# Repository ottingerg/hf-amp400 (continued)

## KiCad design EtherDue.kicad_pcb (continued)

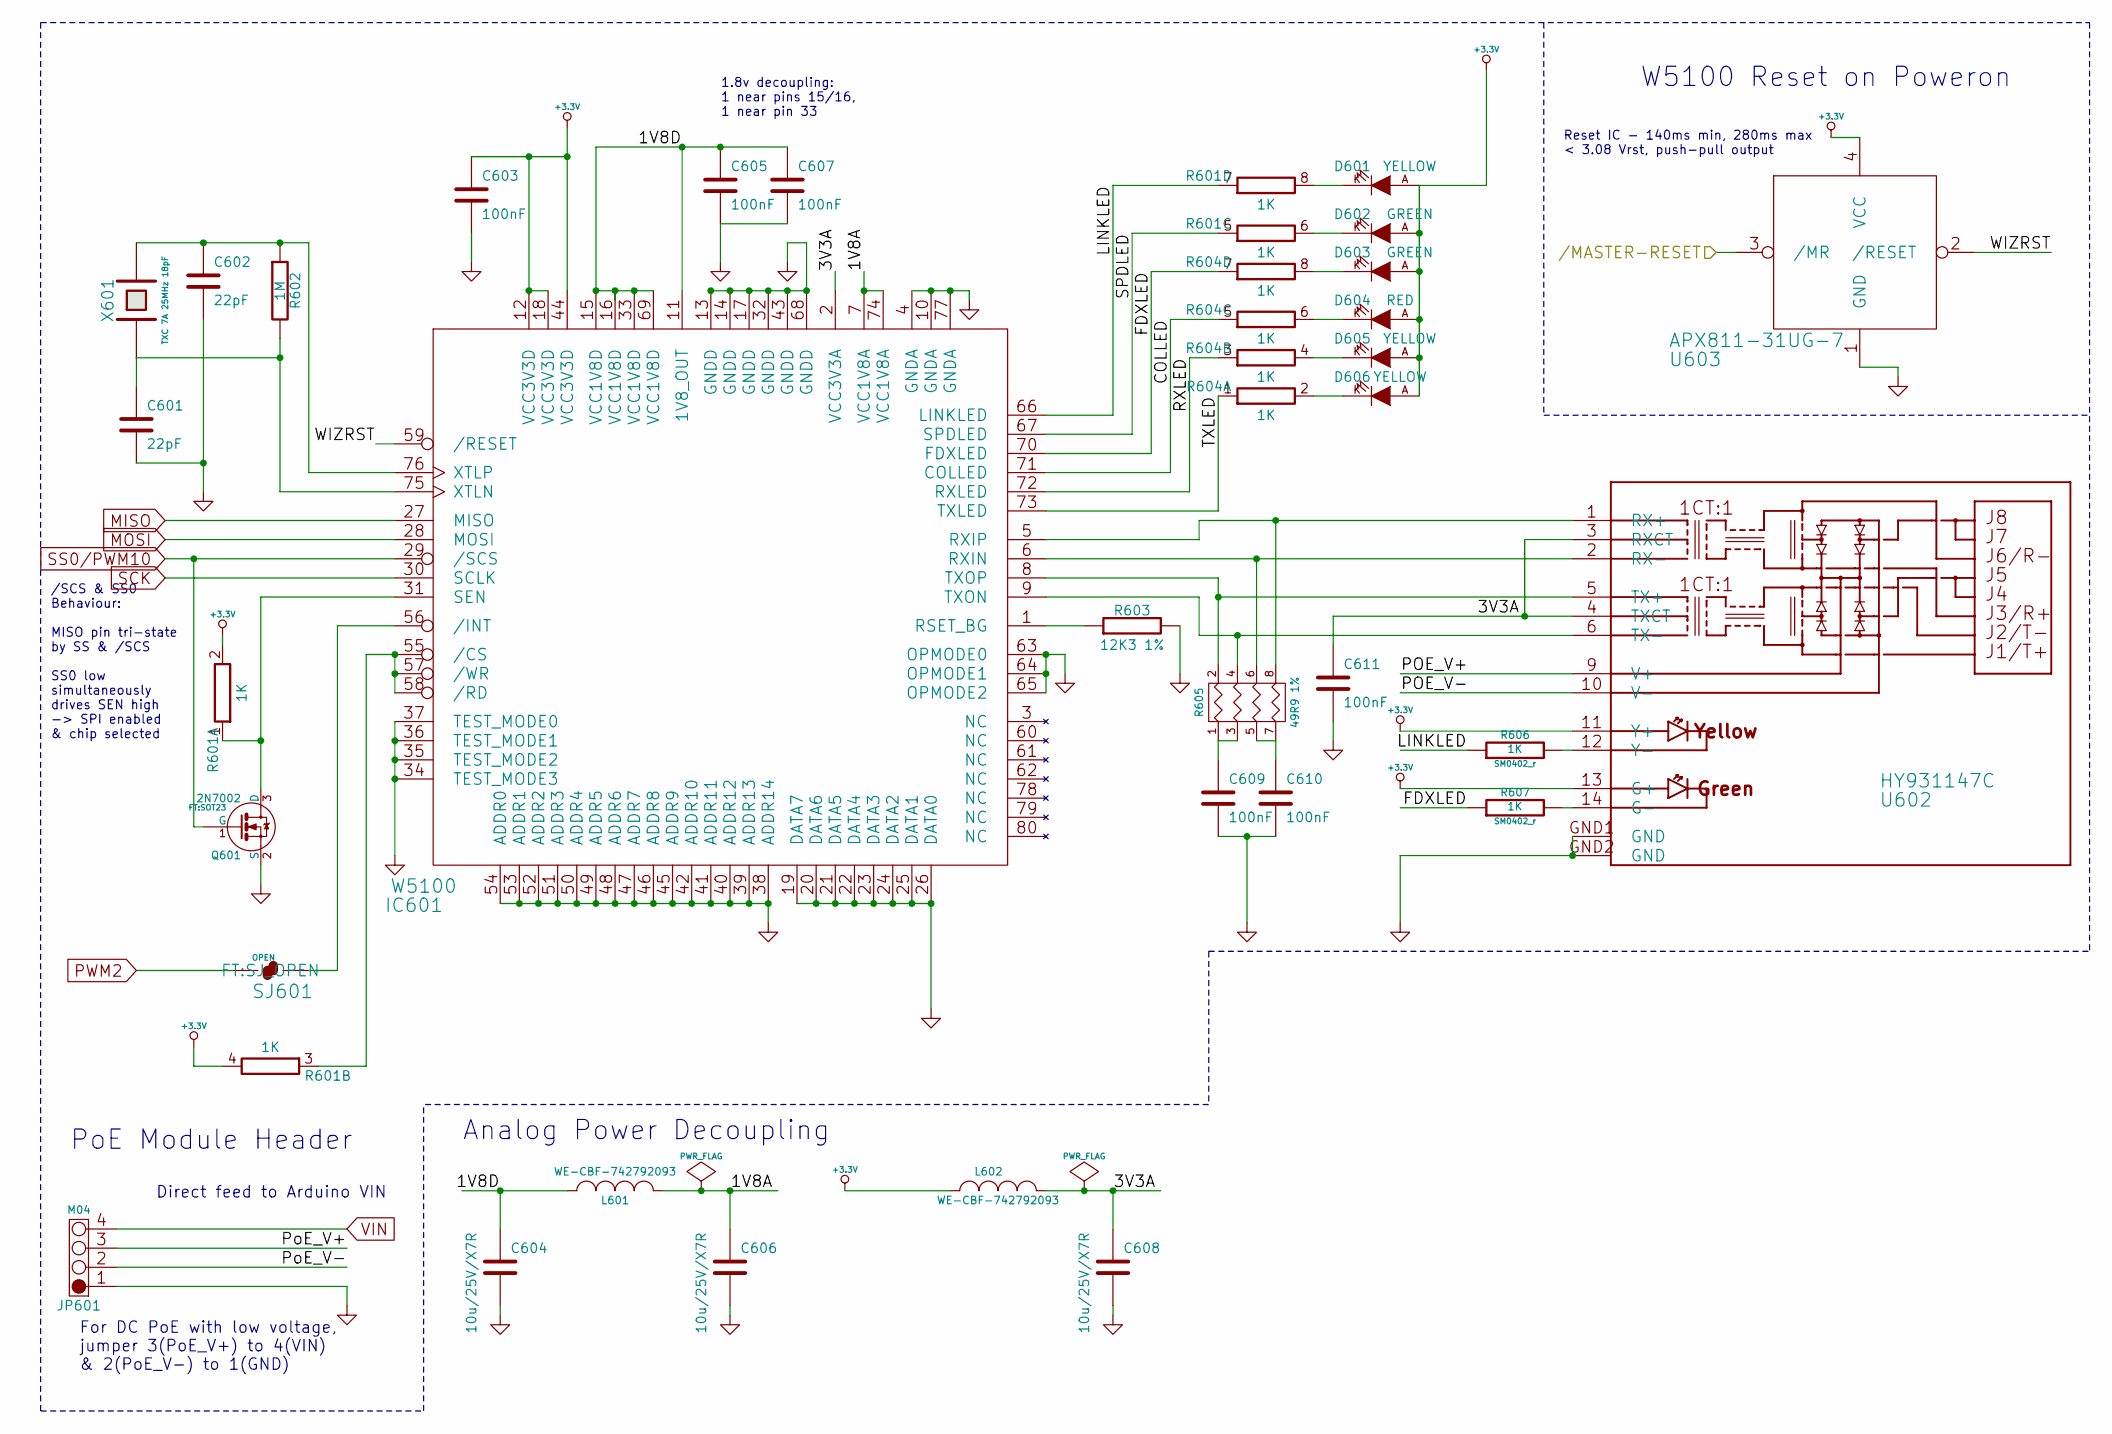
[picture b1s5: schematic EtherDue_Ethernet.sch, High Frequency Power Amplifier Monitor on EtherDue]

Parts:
C601, C602: 22pF; SM0402
C603, C605, C607, C609, C610, C611: 100nF; SM0402
C604, C606, C608: 10u/25V/X7R; SMD-1206_Pol
D601, D605, D606: YELLOW; LED-0603
D602, D603: GREEN; LED-0603
D604: RED; LED-0603
IC601: W5100; SQFP80
JP601: M04; FT-POE-MODULE-NOOUTLINE
L601, L602: WE-CBF-742792093; 0805
Q601: 2N7002; SOT23
R601, R604: 1K; RES_CAY16
R602: 1M; SM0402_r
R603: 12K3 1%; SM0402_r
R605: 49R9 1%; RES_CAY16
R606, R607: 1K; SM0402_r
SJ601: OPEN; SJ_OPEN
U602: HY931147C
U603: APX811-31UG-7; SOT143-R
X601: TXC 7A 25MHz 18pF; TXC_7A

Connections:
+3.3V: C603.1, D601.A, D602.A, D603.A, D604.A, D605.A, D606.A, IC601.12 (VCC3V3D), IC601.18 (VCC3V3D), IC601.44 (VCC3V3D), L602.1, R601.2 (8), R601.4 (8), U602.11 (Y+), U602.13 (G+), U603.4 (VCC); also elsewhere on the board
/Connectors//MASTER-RESET: U603.3 (/MR); also elsewhere on the board
/Ethernet/1V8A: C606.1, IC601.7 (VCC1V8A), IC601.74 (VCC1V8A), L601.2
/Ethernet/1V8D: C604.1, C605.1, C607.1, IC601.11 (1V8_OUT), IC601.15 (VCC1V8D), IC601.16 (VCC1V8D), IC601.33 (VCC1V8D), IC601.69 (VCC1V8D), L601.1
/Ethernet/3V3A: C608.1, C611.1, IC601.2 (VCC3V3A), L602.2, U602.3 (RXCT), U602.4 (TXCT)
/Ethernet/COLLED: IC601.71 (COLLED), R604.5 (7)
/Ethernet/FDXLED: IC601.70 (FDXLED), R604.7, R607.1
/Ethernet/LINKLED: IC601.66 (LINKLED), R601.7, R606.1
/Ethernet/POE_V+: JP601.3, U602.9 (V+)
/Ethernet/POE_V-: JP601.2, U602.10 (V-)
/Ethernet/RXLED: IC601.72 (RXLED), R604.3 (7)
/Ethernet/SPDLED: IC601.67 (SPDLED), R601.5 (7)
/Ethernet/TXLED: IC601.73 (TXLED), R604.1 (7)
/Ethernet/WIZRST: IC601.59 (/RESET), U603.2 (/RESET)
MISO: IC601.27 (MISO); also elsewhere on the board
MOSI: IC601.28 (MOSI); also elsewhere on the board
unnamed: C601.1, IC601.75 (XTLN), R602.2, X601.1
unnamed: C602.1, IC601.76 (XTLP), R602.1, X601.2
unnamed: C609.1, R605.1, R605.3 (P2)
unnamed: C610.1, R605.5 (P3), R605.7 (P4)
unnamed: D601.K, R601.8
unnamed: D602.K, R601.6 (8)
unnamed: D603.K, R604.8
unnamed: D604.K, R604.6 (8)
unnamed: D605.K, R604.4 (8)
unnamed: D606.K, R604.2 (8)
unnamed: IC601.1 (RSET_BG), R603.1
unnamed: IC601.5 (RXIP), R605.8 (R4), U602.1 (RX+)
unnamed: IC601.6 (RXIN), R605.6 (R3), U602.2 (RX-)
unnamed: IC601.8 (TXOP), R605.2 (R1), U602.5 (TX+)
unnamed: IC601.9 (TXON), R605.4 (R1), U602.6 (TX-)
unnamed: IC601.31 (SEN), Q601.3 (D), R601.1 (7)
unnamed: IC601.55 (/CS), IC601.57 (/WR), IC601.58 (/RD), R601.3 (7)
unnamed: IC601.56 (/INT), SJ601.2
unnamed: R606.2, U602.12 (Y-)
unnamed: R607.2, U602.14 (G-)
PWM2: SJ601.1; also elsewhere on the board
SCK: IC601.30 (SCLK); also elsewhere on the board
SS0/PWM10: IC601.29 (/SCS), Q601.1 (G); also elsewhere on the board
VIN: JP601.4; also elsewhere on the board

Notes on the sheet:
W5100 Reset on Poweron
Analog Power Decoupling
For DC PoE with low voltage, jumper 3(PoE_V+) to 4(VIN) & 2(PoE_V-) to 1(GND)
Direct feed to Arduino VIN
PoE Module Header
1.8v decoupling: 1 near pins 15/16, 1 near pin 33
/SCS & SS0 Behaviour: MISO pin tri-state by SS & /SCS SS0 low simultaneously drives SEN high -> SPI enabled & chip selected
Reset IC - 140ms min, 280ms max < 3.08 Vrst, push-pull output

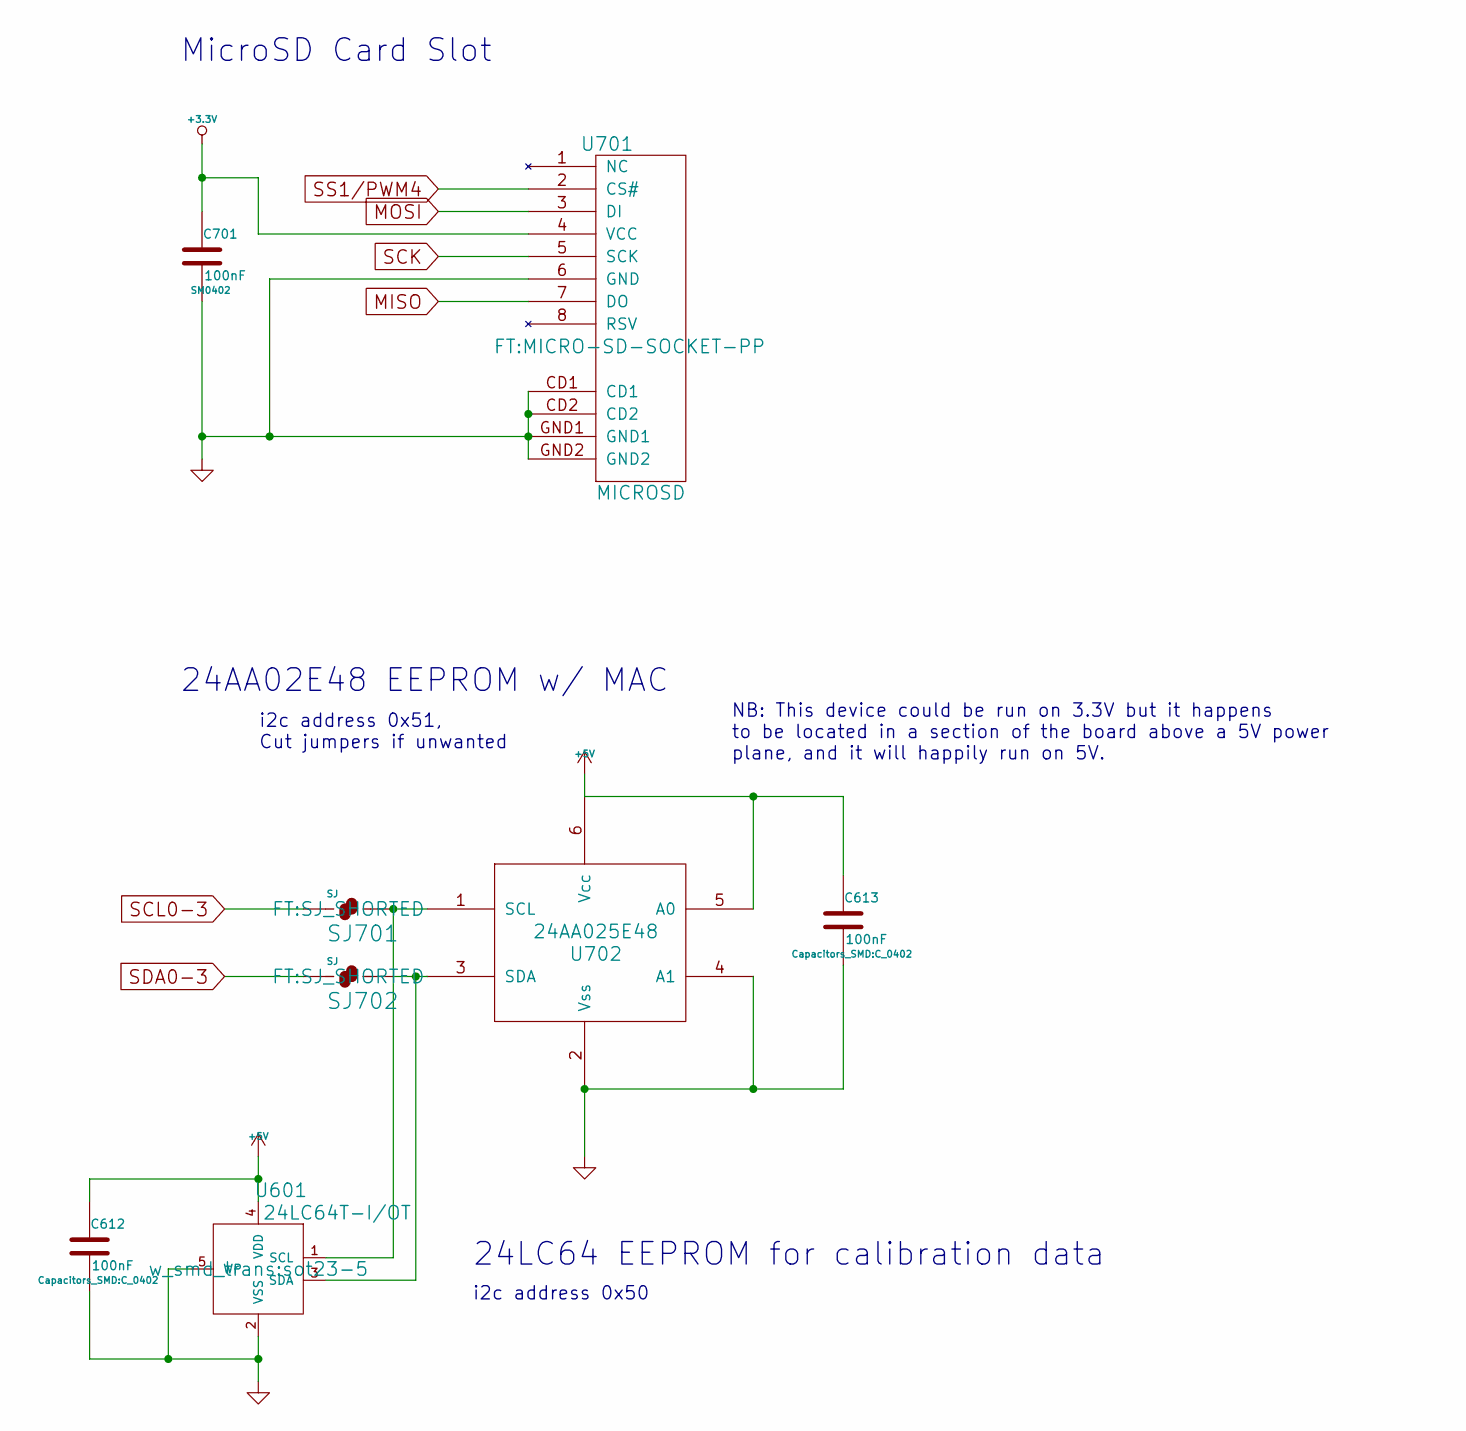
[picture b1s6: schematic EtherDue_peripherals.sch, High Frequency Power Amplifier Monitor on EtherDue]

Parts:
C612, C613: 100nF; C_0402
C701: 100nF; SM0402
SJ701, SJ702: SJ; SJ_SHORTED
U601: 24LC64T-I/OT; sot23-5
U701: MICROSD; MICRO-SD-SOCKET-PP
U702: 24AA025E48; SOT23-6

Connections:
+3.3V: C701.1, U701.4 (VCC); also elsewhere on the board
+5V: C612.1, C613.1, U601.4 (VDD), U702.5 (A0), U702.6 (Vcc); also elsewhere on the board
MISO: U701.7 (DO); also elsewhere on the board
MOSI: U701.3 (DI); also elsewhere on the board
unnamed: SJ701.2, U601.1 (SCL), U702.1 (SCL)
unnamed: SJ702.2, U601.3 (SDA), U702.3 (SDA)
SCK: U701.5 (SCK); also elsewhere on the board
SCL0-3: SJ701.1; also elsewhere on the board
SDA0-3: SJ702.1; also elsewhere on the board
SS1/PWM4: U701.2 (CS#); also elsewhere on the board

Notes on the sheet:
24AA02E48 EEPROM w/ MAC
i2c address 0x51, Cut jumpers if unwanted
MicroSD Card Slot
NB: This device could be run on 3.3V but it happens to be located in a section of the board above a 5V power plane, and it will happily run on 5V.
24LC64 EEPROM for calibration data
i2c address 0x50

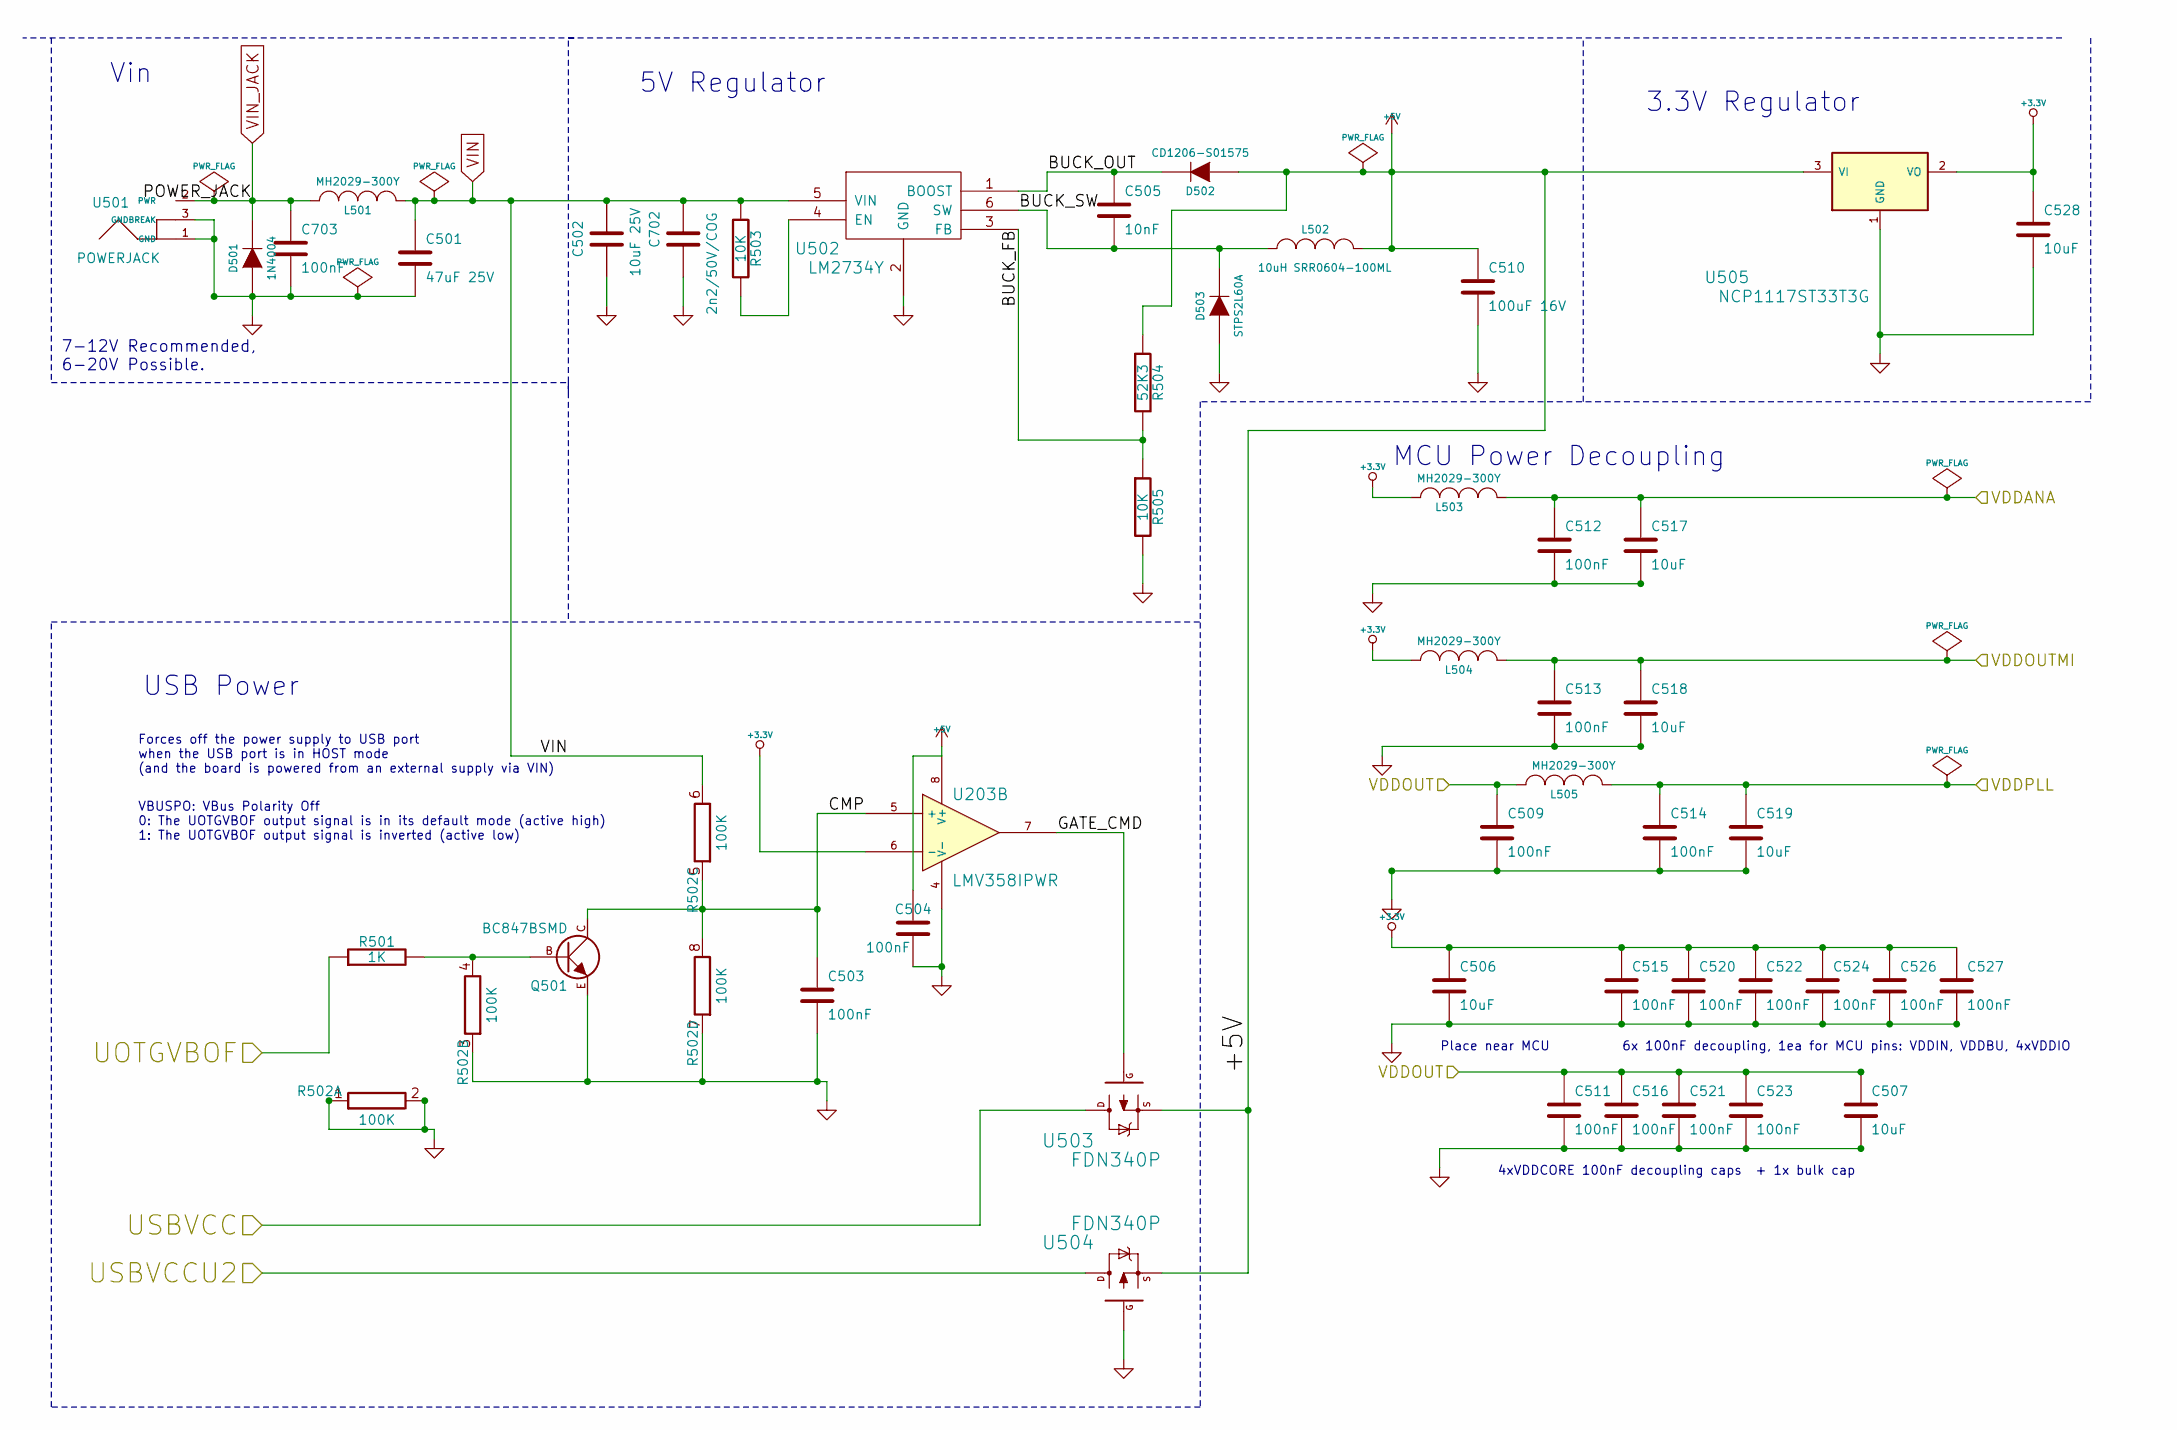
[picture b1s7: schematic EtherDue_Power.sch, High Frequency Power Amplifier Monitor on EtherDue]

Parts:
C501: 47uF 25V; c_elec_6.3x5.8
C502: 10uF 25V; SM1206
C503, C504, C509, C511, C512, C513, C514, C515, C516, C520, C521, C522, C523, C524, C526, C527: 100nF; SM0402
C505: 10nF; SM0402
C506, C507, C517, C518, C519, C528: 10uF; SM0603_Capa
C510: 100uF 16V; c_elec_6.3x5.8
C702: 2n2/50V/COG; C_0603
C703: 100nF; SM0603_Capa
D501: 1N4004; SMB-DIODE
D502: CD1206-S01575; 1206_DIODE
D503: STPS2L60A; SMA-DIODE
L501, L503, L504, L505: MH2029-300Y; MH2029
L502: 10uH SRR0604-100ML; SRR0604
Q501: BC847BSMD; SOT23_TRANSISTOR
R501: 1K; SM0402_r
R502: 100K; RES_CAY16
R503, R505: 10K; SM0402_r
R504: 52K3; SM0402_r
U203: LMV358IPWR; TSSOP8
U501: POWERJACK; POWER_JACK_PTH
U502: LM2734Y; SOT23-6
U503, U504: FDN340P; SOT23_MOSFET
U505: NCP1117ST33T3G; SOT223

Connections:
+3.3V: C506.1, C515.1, C520.1, C522.1, C524.1, C526.1, C527.1, C528.1, L503.1, L504.1, U203.6 (-), U505.2 (VO); also elsewhere on the board
+5V: C504.1, C510.1, D502.A, L502.2, R504.1, U203.8 (V+), U503.S, U504.S, U505.3 (VI); also elsewhere on the board
/Connectors/USBVCC: U503.D; also elsewhere on the board
/MCU/UOTGVBOF: R501.1; also elsewhere on the board
/MCU/VDDANA: C512.1, C517.1, L503.2; also elsewhere on the board
/MCU/VDDOUT: C507.1, C509.1, C511.1, C516.1, C521.1, C523.1, L505.1; also elsewhere on the board
/MCU/VDDOUTMI: C513.1, C518.1, L504.2; also elsewhere on the board
/MCU/VDDPLL: C514.1, C519.1, L505.2; also elsewhere on the board
/Mega16U2/USBVCCU2: U504.D; also elsewhere on the board
/Power/BUCK_FB: R504.2, R505.1, U502.3 (FB)
/Power/BUCK_OUT: C505.1, D502.K, U502.1 (BOOST)
/Power/BUCK_SW: C505.2, D503.K, L502.1, U502.6 (SW)
/Power/CMP: C503.1, Q501.C, R502.5 (7), R502.8, U203.5 (+)
/Power/GATE_CMD: U203.7, U503.G
unnamed: Q501.B, R501.2, R502.4 (8)
unnamed: R503.2, U502.4 (EN)
VIN: C501.1, C502.1, C702.1, L501.2, R502.6 (8), R503.1, U502.5 (VIN); also elsewhere on the board
VIN_JACK: C703.1, D501.K, L501.1, U501.2 (PWR); also elsewhere on the board

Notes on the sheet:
4xVDDCORE 100nF decoupling caps + 1x bulk cap
Place near MCU
6x 100nF decoupling, 1ea for MCU pins: VDDIN, VDDBU, 4xVDDIO
MCU Power Decoupling
VBUSPO: VBus Polarity Off 0: The UOTGVBOF output signal is in its default mode (active high) 1: The UOTGVBOF output signal is inverted (active low)
Forces off the power supply to USB port when the USB port is in HOST mode (and the board is powered from an external supply via VIN)
USB Power
3.3V Regulator
5V Regulator
Vin
7-12V Recommended, 6-20V Possible.

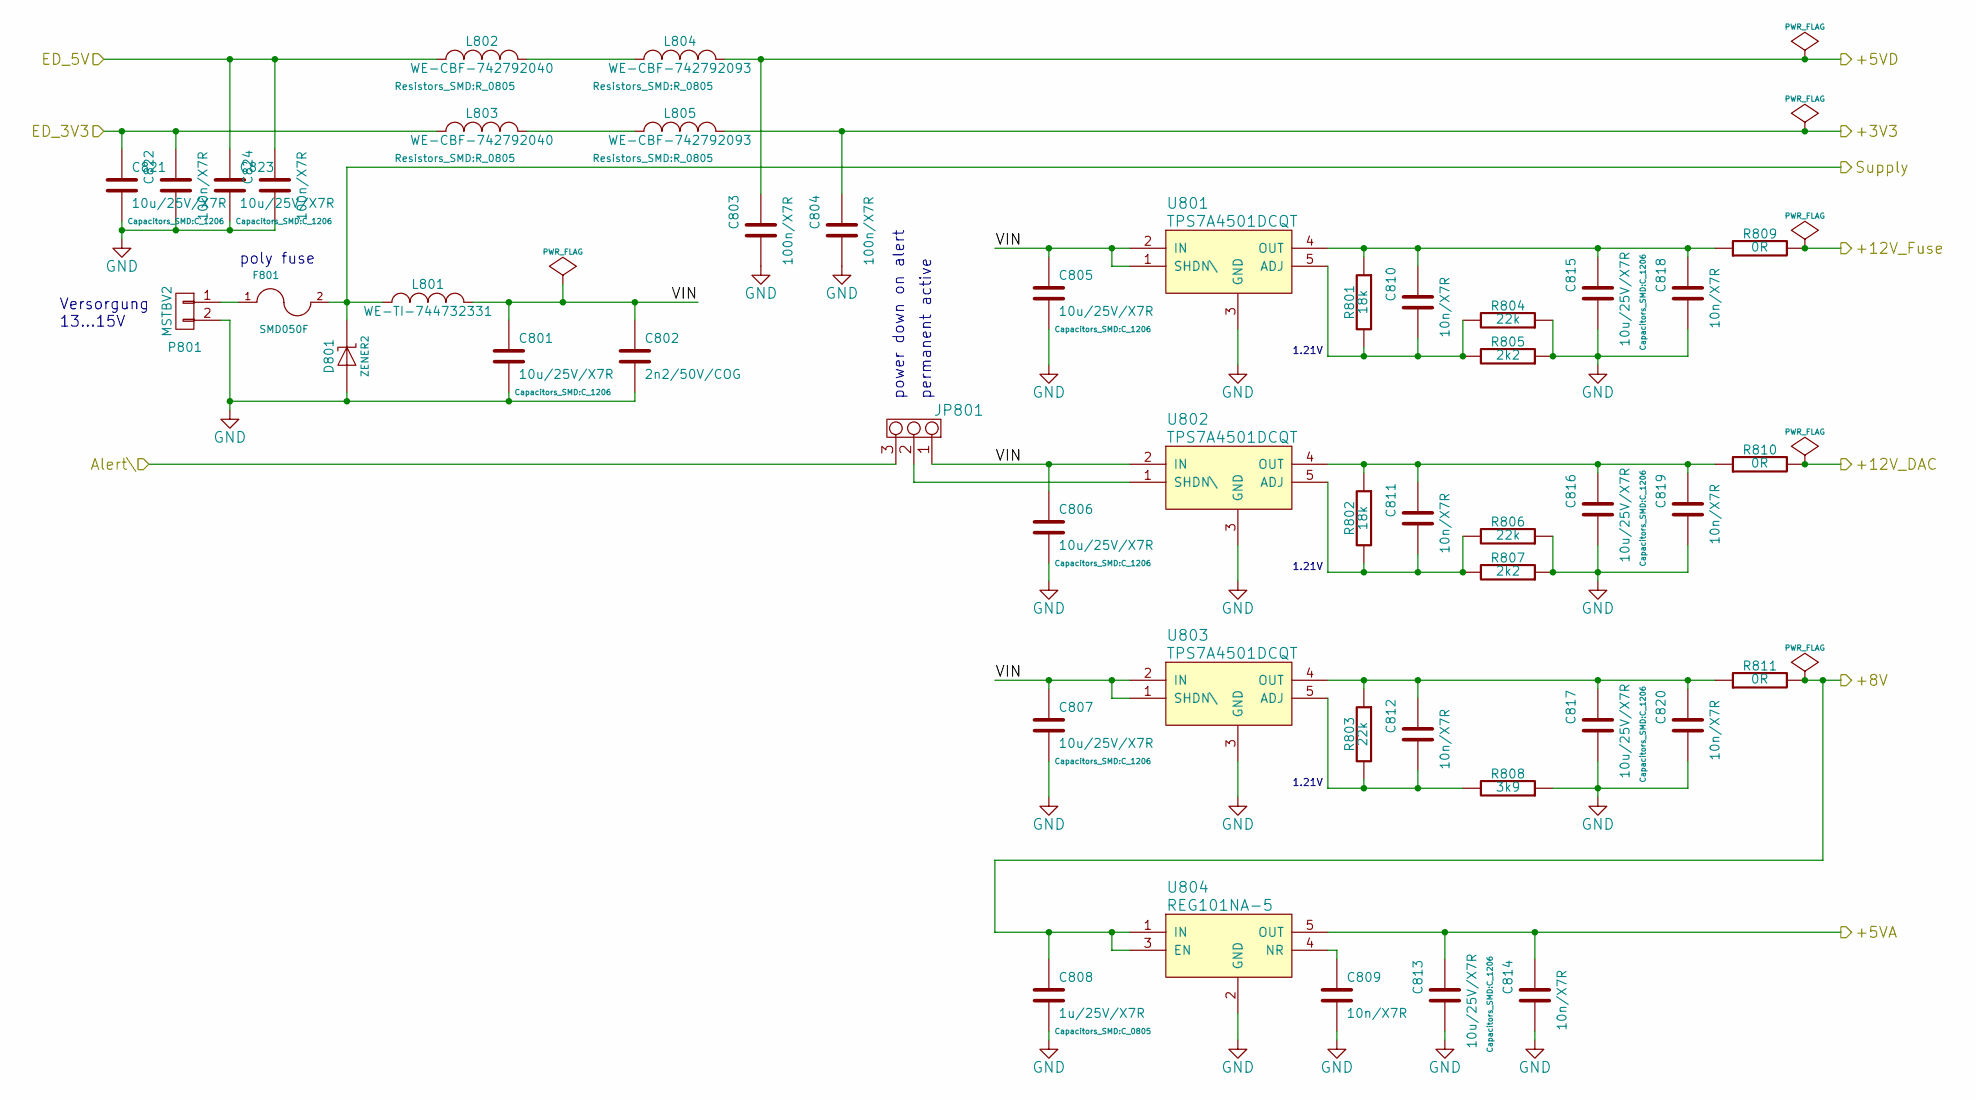
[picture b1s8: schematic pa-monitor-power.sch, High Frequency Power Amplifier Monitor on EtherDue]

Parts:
C801, C805, C806, C807, C813, C815, C816, C817, C821, C823: 10u/25V/X7R; C_1206
C802: 2n2/50V/COG; C_0603
C803, C804, C822, C824: 100n/X7R; C_0603
C808: 1u/25V/X7R; C_0805
C809, C810, C811, C812, C814, C818, C819, C820: 10n/X7R; C_0603
D801: ZENER2; Diode-SMB_Standard
F801: SMD050F
JP801: JUMPER3; Pin_Header_Straight_1x03
L801: WE-TI-744732331; WE-TI_8075_SHRINKTUBE
L802, L803: WE-CBF-742792040; R_0805
L804, L805: WE-CBF-742792093; R_0805
P801: MSTBV2
R801, R802: 18k; R_0603
R803, R804, R806: 22k; R_0603
R805, R807: 2k2; R_0603
R808: 3k9; R_0603
R809, R810, R811: 0R; R_0603
U801, U802, U803: TPS7A4501DCQT; DCQ(R-PDSO-G6)
U804: REG101NA-5; DBV(R-PDSO-G5)

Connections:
+3.3V: C821.1, C822.1, L803.1; also elsewhere on the board
+5V: C823.1, C824.1, L802.1; also elsewhere on the board
/Analog I/O/+3V3: C804.1, L805.2; also elsewhere on the board
/Analog I/O/+5VA: C813.1, C814.1, U804.5 (OUT); also elsewhere on the board
/Analog I/O/+12V: R810.2; also elsewhere on the board
/CAN-Bus/+5V: C803.1, L804.2; also elsewhere on the board
/PA-Monitor Power Supply/+8V: C808.1, R811.2, U804.1 (IN), U804.3 (EN); also elsewhere on the board
/PA-Monitor Power Supply/VIN: C801.1, C802.1, C805.1, C806.1, C807.1, JP801.1, L801.2, U801.1 (SHDN\), U801.2 (IN), U802.2 (IN), U803.1 (SHDN\), U803.2 (IN)
unnamed: C809.1, U804.4 (NR)
unnamed: C810.1, C815.1, C818.1, R801.1, R809.1, U801.4 (OUT)
unnamed: C810.2, R801.2, R804.2, R805.2, U801.5 (ADJ)
unnamed: C811.1, C816.1, C819.1, R802.1, R810.1, U802.4 (OUT)
unnamed: C811.2, R802.2, R806.2, R807.2, U802.5 (ADJ)
unnamed: C812.1, C817.1, C820.1, R803.1, R811.1, U803.4 (OUT)
unnamed: C812.2, R803.2, R808.2, U803.5 (ADJ)
unnamed: F801.1, P801.1
unnamed: JP801.2, U802.1 (SHDN\)
unnamed: L802.2, L804.1
unnamed: L803.2, L805.1
PIN24: JP801.3; also elsewhere on the board
VIN_JACK: D801.K, F801.2, L801.1; also elsewhere on the board

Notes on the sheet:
Versorgung 13...15V
1.21V
power down on alert
permanent active
poly fuse

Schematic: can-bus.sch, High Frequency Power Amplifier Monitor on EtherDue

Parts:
C901, C902: 100n/X7R; C_0603
L901: WE-SL1-744212510; WE-SL1
P901, P902: 677006144621; Firewire-Female-WE677006144621
R901: 1k8; R_0603
R902: 1k; R_0603
R903: 47k; R_0603
R904, R905: 60R; R_0805
R906, R907: 1k3; R_0805
SJ901, SJ902: Solder-Jumper; SJ_2W
U901: TJA1040T; SOIC-8_3.9x4.9mm_Pitch1.27mm

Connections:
/CAN-Bus/+5V: C901.1, U901.3 (VCC); also elsewhere on the board
CANRX0: R901.1, R902.2; also elsewhere on the board
CANTX0: U901.1 (TXD); also elsewhere on the board
unnamed: C902.1, SJ901.C, SJ902.C, U901.5 (SPLIT)
unnamed: L901.1 (AA), R904.2, R906.2, U901.7 (CANH)
unnamed: L901.3 (SA), R905.2, R907.2, U901.6 (CANL)
unnamed: L901.4 (SB), P901.3, P902.3
unnamed: L901.5 (AB), P901.4, P902.4
unnamed: R902.1, U901.4 (RXD)
unnamed: R903.1, U901.8 (STB)
unnamed: R904.1, SJ901.1
unnamed: R905.1, SJ901.2
unnamed: R906.1, SJ902.1
unnamed: R907.1, SJ902.2

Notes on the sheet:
Firewire Connectors are used for CAN
Level shift 5V to 3.3V

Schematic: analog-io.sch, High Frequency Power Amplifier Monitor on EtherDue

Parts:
C1001, C1002, C1003, C1004, C1009, C1010, C1017, C1018, C1022, C1023, C1034, C1035, C1036, C1037, C1038, C1039, C1040, C1041: 1n/X7R; C_0603
C1005, C1007, C1011, C1014: 100p/X7R; C_0603
C1006, C1008, C1012, C1015, C1016, C1019, C1020, C1021, C1024, C1025, C1028, C1029, C1030, C1031, C1032: 100n/X7R; C_0603
C1013, C1026, C1033: 10u/25V/X7R; C_1206
C1042: 10n/X7R; C_0603
D1001, D1002, D1003, D1004: BAT54S; sot23
JP1001, JP1002, JP1003, JP1004: JUMPER3; Pin_Header_Straight_1x03
LED1001: RED; LED-0805
Q1001: BSS308; sot23-gsd
R1001, R1002, R1003, R1004, R1005, R1006, R1007, R1008, R1014, R1015: 100R; R_0603
R1009, R1010, R1011, R1012: 5k6; R_0603
R1013, R1016, R1017: 4k7; R_0603
R1018, R1019: 33R; R_0603
U1001: AD7294BSUZ; QFP40P900X900X120-64N
VR1001, VR1002, VR1003, VR1004: 10k; Potentiometer_Bourns_3296W_3-8Zoll_Inline_ScrewUp
X1001, X1002, X1003, X1004, X1005, X1006, X1007, X1008, X1009, X1010, X1011, X1012: SMB; SMB-RS#420-5401_wirepad

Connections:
/Analog I/O/+3V3: C1032.1, Q1001.S, R1013.2, R1016.2, R1017.2, U1001.42 (VDRIVE); also elsewhere on the board
/Analog I/O/+5VA: C1003.1, C1009.1, C1013.1, C1016.1, C1017.1, C1019.1, C1021.1, C1022.1, C1025.1, C1029.1, D1001.3 (cathode), D1002.3 (cathode), D1003.3 (cathode), D1004.3 (cathode), U1001.5 (AVDD1), U1001.8 (AVDD2), U1001.14 (AVDD3), U1001.25 (AVDD4), U1001.56 (AVDD5), U1001.57 (AVDD6); also elsewhere on the board
/Analog I/O/+12V: C1020.1, C1024.1, C1031.1, R1009.2, R1010.2, R1011.2, R1012.2, U1001.21 (DAC_OUTV+_AB), U1001.28 (DAC_OUTV+_CD); also elsewhere on the board
/Analog I/O/VIN1: C1009.2, C1010.1, C1039.1, D1002.2 (AK), U1001.51 (VIN1); also elsewhere on the board
/Analog I/O/VIN3: C1022.2, C1023.1, C1041.1, D1004.2 (AK), U1001.49 (VIN3); also elsewhere on the board
/Analog Level Adoption/I_Fuse1_Out: C1003.2, C1004.1, C1038.1, D1001.2 (AK), U1001.52 (VIN0); also elsewhere on the board
/Analog Level Adoption/I_Fuse2_Out: C1017.2, C1018.1, C1040.1, D1003.2 (AK), U1001.50 (VIN2); also elsewhere on the board
/CAN-Bus/+5V: C1028.1, U1001.44 (DVDD); also elsewhere on the board
unnamed: C1001.1, C1005.1, R1001.2, U1001.12 (D1-)
unnamed: C1001.2, C1007.1, R1002.2, U1001.11 (D1+)
unnamed: C1002.1, C1014.1, R1003.2, U1001.10 (D2+)
unnamed: C1002.2, C1011.1, R1004.2, U1001.9 (D2-)
unnamed: C1006.1, JP1001.2, R1005.2, U1001.18 (OFFSET_IN_A)
unnamed: C1008.1, JP1002.2, R1006.2, U1001.23 (OFFSET_IN_B)
unnamed: C1012.1, JP1003.2, R1007.2, U1001.26 (OFFSET_IN_C)
unnamed: C1015.1, JP1004.2, R1008.2, U1001.31 (OFFSET_IN_D)
unnamed: C1026.1, U1001.53 (REF_ADC)
unnamed: C1030.1, U1001.54 (DCAP)
unnamed: C1033.1, C1042.1, U1001.15 (REF_DAC)
unnamed: C1034.1, U1001.19 (VOUT_A), X1009.2 (center)
unnamed: C1035.1, U1001.22 (VOUT_B), X1010.2 (center)
unnamed: C1036.1, U1001.27 (VOUT_C), X1011.2 (center)
unnamed: C1037.1, U1001.30 (VOUT_D), X1012.2 (center)
unnamed: JP1001.3, R1009.1, VR1001.2, VR1001.3
unnamed: JP1002.3, R1010.1, VR1002.2, VR1002.3
unnamed: JP1003.3, R1011.1, VR1003.2, VR1003.3
unnamed: JP1004.3, R1012.1, VR1004.2, VR1004.3
unnamed: LED1001.A, R1015.1
unnamed: Q1001.D, R1015.2
unnamed: Q1001.G, R1014.2
unnamed: R1001.1, X1001.2 (center)
unnamed: R1002.1, X1002.2 (center)
unnamed: R1003.1, X1003.2 (center)
unnamed: R1004.1, X1004.2 (center)
unnamed: R1005.1, X1005.2 (center)
unnamed: R1006.1, X1006.2 (center)
unnamed: R1007.1, X1007.2 (center)
unnamed: R1008.1, X1008.2 (center)
unnamed: R1016.1, R1018.2, U1001.39 (SDA)
unnamed: R1017.1, R1019.2, U1001.40 (SCL)
PIN24: R1013.1, R1014.1, U1001.35 (ALERT\); also elsewhere on the board
SCL0-3: R1019.1; also elsewhere on the board
SDA0-3: R1018.1; also elsewhere on the board

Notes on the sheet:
Shielded Inputs Temperature Sensors
Shielded Inputs for Offset
Shielded Outputs for Gate-Biasing
I2C Address: 0x61
unused highside current amp
TODO: R berechnen
10-turn potentiometers

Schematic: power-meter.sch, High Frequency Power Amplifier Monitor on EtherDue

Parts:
C1101, C1102: 100n/X7R; C_0603
C1103, C1104: 100p/X7R; C_0603
C1105, C1107: 47n/C0G; C_0805
C1106, C1109, C1113, C1114: 10n/X7R; C_0603
C1108, C1112: 10u/25V/X7R; C_1206
C1110: 47p/C0G; C_0603
C1111: 100n/X7R; C_0805
L1101: WE-CBF-742792093; R_0805
P1101, P1102: CONN_01X02; Pin_Header_Straight_1x02
R1101: 52R3/1%; R_0805
R1103, R1106: 0R; R_0603
R1104: 12k; R_0805
R1105: 2k2; R_0805
U1101: ADL5513; LFCSP16
U1102: REG101NA-5; DBV(R-PDSO-G5)
X1101: SMA; SMA-RS#616-3422
X1102, X1103: SMB; SMB-RS#420-5401_wirepad

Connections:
/PA-Monitor Power Supply/+8V: C1112.1, P1101.2, P1102.2, U1102.1 (IN), U1102.3 (EN); also elsewhere on the board
/Power-Meter Forward 1/+5V_PM: C1106.1, C1108.1, L1101.1, R1104.2, U1102.5 (OUT)
AD0: C1114.1, R1106.2; also elsewhere on the board
unnamed: C1101.1, C1102.1, C1103.1, C1104.1, L1101.2, U1101.1 (VPOS1), U1101.4 (VPOS2)
unnamed: C1105.1, U1101.2 (IN_HI)
unnamed: C1105.2, R1101.2, X1101.2 (center)
unnamed: C1107.1, U1101.3 (IN_LO)
unnamed: C1109.1, U1102.4 (NR)
unnamed: C1110.2, U1101.14 (CLPF)
unnamed: C1111.1, R1104.1, R1105.2, U1101.9 (TADJ)
unnamed: C1113.1, R1103.2, R1106.1, U1101.12 (VOUT), X1102.2 (center), X1103.2 (center)
unnamed: R1103.1, U1101.11 (VSET)

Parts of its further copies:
C1201, C1202, C1302, C1401, C1402, C1802, C1803: 100n/X7R; C_0603
C1203, C1204, C1303, C1304, C1403, C1404, C1605: 100p/X7R; C_0603
C1205, C1207, C1305, C1307, C1405, C1407, C1606: 47n/C0G; C_0805
C1206, C1209, C1213, C1214, C1306, C1309, C1313, C1314, C1406, C1409, C1413, C1414, C1607, C1609, C1613, C1614, C1713, C1714, C1813, C1814: 10n/X7R; C_0603
C1208, C1212, C1308, C1312, C1408, C1412, C1608: 10u/25V/X7R; C_1206
C1210, C1310, C1410, C1610: 47p/C0G; C_0603
C1211, C1311, C1411, C1611, C1711, C1811: 100n/X7R; C_0805
L1201, L1301, L1401, L1601, L1801: WE-CBF-742792093; R_0805
P1201, P1202, P1301, P1302, P1401, P1402, P1601, P1602, P1701, P1702, P1801, P1802: CONN_01X02; Pin_Header_Straight_1x02
R1201, R1401: 52R3/1%; R_0805
R1203, R1206, R1303, R1306, R1403, R1406: 0R; R_0603
R1204, R1304, R1404: 12k; R_0805
R1205, R1305, R1405: 2k2; R_0805
U1201, U1301, U1401, U1601: ADL5513; LFCSP16
U1202, U1302, U1402, U1602: REG101NA-5; DBV(R-PDSO-G5)
X1201, X1301, X1401, X1601, X1701, X1801: SMA; SMA-RS#616-3422
X1202, X1203, X1302, X1303, X1402, X1403, X1602, X1603, X1702, X1703, X1802, X1803: SMB; SMB-RS#420-5401_wirepad

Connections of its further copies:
/Analog I/O/VIN1: C1314.1, R1306.2; also elsewhere on the board
/Analog I/O/VIN3: C1414.1, R1406.2; also elsewhere on the board
/PA-Monitor Power Supply/+8V: C1212.1, C1312.1, C1412.1, P1201.2, P1202.2, P1301.2, P1302.2, P1401.2, P1402.2, U1202.1 (IN), U1202.3 (EN), U1302.1 (IN), U1302.3 (EN), U1402.1 (IN), U1402.3 (EN); also elsewhere on the board
/Power-Meter Forward 2/+5V_PM: C1206.1, C1208.1, L1201.1, R1204.2, U1202.5 (OUT)
/Power-Meter Return 1/+5V_PM: C1306.1, C1308.1, L1301.1, R1304.2, U1302.5 (OUT)
/Power-Meter Return 2/+5V_PM: C1406.1, C1408.1, L1401.1, R1404.2, U1402.5 (OUT)
AD1: C1214.1, R1206.2; also elsewhere on the board
unnamed: C1201.1, C1202.1, C1203.1, C1204.1, L1201.2, U1201.1 (VPOS1), U1201.4 (VPOS2)
unnamed: C1205.1, U1201.2 (IN_HI)
unnamed: C1205.2, R1201.2, X1201.2 (center)
unnamed: C1207.1, U1201.3 (IN_LO)
unnamed: C1209.1, U1202.4 (NR)
unnamed: C1210.2, U1201.14 (CLPF)
unnamed: C1211.1, R1204.1, R1205.2, U1201.9 (TADJ)
unnamed: C1213.1, R1203.2, R1206.1, U1201.12 (VOUT), X1202.2 (center), X1203.2 (center)
unnamed: C1305.1, U1301.2 (IN_HI)
unnamed: C1307.1, U1301.3 (IN_LO)
unnamed: C1309.1, U1302.4 (NR)
unnamed: C1310.2, U1301.14 (CLPF)
unnamed: C1311.1, R1304.1, R1305.2, U1301.9 (TADJ)
unnamed: C1313.1, R1303.2, R1306.1, U1301.12 (VOUT), X1302.2 (center), X1303.2 (center)
unnamed: C1401.1, C1402.1, C1403.1, C1404.1, L1401.2, U1401.1 (VPOS1), U1401.4 (VPOS2)
unnamed: C1405.1, U1401.2 (IN_HI)
unnamed: C1405.2, R1401.2, X1401.2 (center)
unnamed: C1407.1, U1401.3 (IN_LO)
unnamed: C1409.1, U1402.4 (NR)
unnamed: C1410.2, U1401.14 (CLPF)
unnamed: C1411.1, R1404.1, R1405.2, U1401.9 (TADJ)
unnamed: C1413.1, R1403.2, R1406.1, U1401.12 (VOUT), X1402.2 (center), X1403.2 (center)
unnamed 203: L1801.1; also elsewhere on the board
unnamed 276: L1801.2; also elsewhere on the board
unnamed: R1203.1, U1201.11 (VSET)
unnamed: R1303.1, U1301.11 (VSET)
unnamed: R1403.1, U1401.11 (VSET)

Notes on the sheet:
perforated break away
Power supply
measured power
0.4..2.2V
+5V

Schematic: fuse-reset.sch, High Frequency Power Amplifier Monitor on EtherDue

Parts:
C1501, C1504: 100n/X7R; C_0603
C1502: 1u/X7R; C_0805
C1603: 10n/X7R; C_0603
D1501: BAT54S; sot23
Q1501, Q1502: BSS123; sot23-gsd
R1501: 1k; R_0603
R1502: 100k; R_0603
R1503, R1504, R1505: 10k; R_0603
U1501: 4013_with_supply; SOIC-14_3.9x8.7mm_Pitch1.27mm

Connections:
/Analog I/O/+3V3: U1501.14 (VDD); also elsewhere on the board
unnamed: C1501.1, R1501.2
unnamed: C1501.2, D1501.2 (AK)
unnamed: Q1501.G, R1503.2
unnamed: Q1502.G, R1505.1
PIN46: U1501.3 (Cp); also elsewhere on the board
PIN47: C1603.1, U1501.11 (Cp); also elsewhere on the board
PIN48: R1501.1; also elsewhere on the board

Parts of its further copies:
C1505: 10n/X7R; C_0603
C1601, C1604: 100n/X7R; C_0603
C1602: 1u/X7R; C_0805
D1601: BAT54S; sot23
Q1601, Q1602: BSS123; sot23-gsd
R1601: 1k; R_0603
R1602: 100k; R_0603
R1603, R1604, R1605: 10k; R_0603

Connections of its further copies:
/Fuse-Reset B/Reset\: Q1602.D; also elsewhere on the board
unnamed: C1601.1, R1601.2
unnamed: C1601.2, D1601.2 (AK)
unnamed: Q1601.G, R1603.2
unnamed: Q1602.G, R1605.1
PIN46: C1505.1; also elsewhere on the board
PIN49: R1601.1; also elsewhere on the board

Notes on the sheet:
open drain output
asynchronous reset -> monoflop
1kHz
The reset output is pulsed low, when a) a 1kHz (digital, 3.3V) signl is applied to the Enable_AC input and b) a rising edge is applied to Clock input
Decoupling C is on parent sheet
